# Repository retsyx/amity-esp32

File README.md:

# Amity for ESP32

HDMI-CEC that works!

Control your home theater with a familiar remote, and integrate it with Matter and HomeKit home automation.

Read the [rationale](doc/rationale.md), to know why Amity uses HDMI-CEC, and how it works.

This version runs on the Amity ESP32 board. The [original Amity](https://github.com/retsyx/amity) runs on a Raspberry Pi.

## Prerequisites

* An [Amity ESP32 board](hw/README.md) and a USB-C power supply.
* An extra HDMI cable. Amity uses two cables in place of the one connecting your receiver to your TV.
* A remote control. [Couch Clicker Atomic](https://github.com/retsyx/CouchClickerAtomic), [Couch Clicker Atomic 2](https://github.com/retsyx/CouchClickerAtomic2) or a Gen 2/3/4 Siri Remote.
* A Matter compatible home automation system.

## Amity is a flexible HDMI-CEC Controller (Not a Universal Remote)

### The Amity Adapter

Amity connects between home theater componenets using an HDMI Amity adapter. The adapter intercepts HDMI-CEC signals while passing through the HDMI A/V signals untouched. Each adapter has a `Display` HDMI connector that is connected to the display side and a `Source` HDMI connector that is connected to A/V source side.

### Single Adapter Amity

The single adapter Amity is designed for a traditional setup centered around an audio/video receiver (AVR). For example, a TV connected to a receiver output, and various playback devices (i.e. media streamers, blu-ray players, and game consoles, etc.) connected to the receiver's inputs. When changing the source, the input is changed on the receiver. The HDMI-CEC protocol only allows the designated TV to select sources or devices to declare themselves as active sources. TVs do not heed arbitrary source selection commands from other devices. As a result, Amity cannot select inputs on a TV, and cannot control sources connected directly to a TV, including built-in smart TV apps. Similarly, the singla adapter Amity does not support HDMI ARC/eARC. If you use smart TV apps or connect devices, other than a receiver, directly to the TV inputs, Amity is not for your system.

### Multi-Adapter Amity

Amity firmware is designed to support up to four Amity adapters. A multi-adapter Amity enables more applications. It can be used to control a system with two displays (for example, a TV and a projector) connected to a single receiver and to control a system without a receiver, where a TV is connected directly to multiple components, or where some components are connected to the TV and some are connected to a receiver. It can also be used to isolate particularly misbehaved components that demand to be displayed when not appropriate.

### Multi-Amity

Up to four Amities (with four adapters each) can be networked together over WiFi to control a large home theater setup containing more components than a single Amity can control or to control multiple physically separate systems with a single remote.

### Controlling Components Without HDMI-CEC

Amity can only control devices that support HDMI-CEC! However, devices that don't support HDMI-CEC (old game consoles, for example) can still be facilitated.

## Initial Amity Firmware Setup

For a new board, use the provisioning tool to prepare a firmware image and setup card, then install the image over USB. If your board already has Amity installed, continue with [Setup](#setup). To update an existing Amity, see [Firmware Updates](#firmware-updates).

### Download

1. Go to the latest [Amity Release](https://github.com/retsyx/amity-esp32/releases/latest).
2. From the release's **Assets**, download `amity-firmware.zip` and the setup-tool ZIP for your computer:

   | Computer | Setup tool |
   |---|---|
   | Apple Silicon Mac | `amity-provision-darwin-arm64.zip` |
   | Intel Mac | `amity-provision-darwin-amd64.zip` |
   | Windows, Intel/AMD | `amity-provision-windows-amd64.zip` |
   | Windows on ARM | `amity-provision-windows-arm64.zip` |
   | Linux, Intel/AMD | `amity-provision-linux-amd64.zip` |
   | Linux, ARM64 | `amity-provision-linux-arm64.zip` |
3. Extract the setup-tool ZIP into the same folder as `amity-firmware.zip`. Leave the firmware ZIP intact.
4. Open a terminal in that folder, and run the command below.

On macOS or Linux:

```sh
./amity-provision --hostname <amity hostname> --generate-password --out <output folder> amity-firmware.zip
```

On Windows, use PowerShell:

```powershell
.\amity-provision.exe --hostname <amity hostname> --generate-password --out <output folder> amity-firmware.zip
```

Choose a distinct name and output folder for each provisioned board.

The tool creates the output folder, containing:

* `amity-provisioned.bin` — the firmware image for USB installation.
* `amity-pairing.png` — a setup card with the Matter pairing QR code, Matter pairing code, browser address, and generated admin password.
* Text files with the same setup details and password.

For other options, including choosing your own password, see the [Amity provisioning guide](amity-provision/README.md).

If you lose the provisioning information for the board, you will need re-provision, wipe, and re-install the board from scratch!

Continue with [Initial Install over USB](#initial-install-over-usb).

### Build Locally

To build your own firmware, follow the [local build guide](BUILDING.md).

### Initial Install Over USB

1. Connect the Amity board to your computer with a USB data cable.
2. Install [esptool](https://docs.espressif.com/projects/esptool/en/latest/esp32s3/installation.html).
3. Find the board's serial port. Typical names are `COM3` on Windows, `/dev/cu.usbmodem...` on macOS, and `/dev/ttyACM0` on Linux.
4. Run this command with your provisioning output folder:

```sh
esptool --chip esp32s3 --port <port>> write-flash --flash-mode dio --flash-freq 80m --flash-size 8MB 0x0 <output folder>/amity-provisioned.bin
```

If the `esptool` command is unavailable, use `python3 -m esptool` on macOS/Linux, or `python -m esptool` on Windows, in its place.

**Installing this full image replaces all existing settings and pairings.** Use it for initial installation only. Later browser updates use a different file, `amity-update.bin`.

Installation is now done, and Amity can now be setup for use in your home theater.

## Setup

### HDMI Connections

Enable HDMI-CEC on all the home theater system components. Manufacturers use different names for this setting; check your equipment's setup menus.

#### Single Adapter Amity

The single adapter Amity connects between the TV and the receiver.

1. Disconnect the HDMI cable connecting the TV's input to the receiver's output.
2. Connect the TV's HDMI input to the Amity HDMI port marked `Display`.
3. Use a second HDMI cable to connect the receiver's HDMI output to the Amity HDMI port marked `Source`.
4. Leave the playback devices connected to the receiver's inputs.

#### Multi-Adapter Amity

There are many options for connecting a multi-adapter Amity. Generally, there will be at least one between the display and other components, whether with a receiver or without. In addition an adapter can be connected between a receiver and a component to isolate a misbehaving component. In all cases, the 'Display' side of an adapter should be connected towards the display, and the 'Source' side of an adapter should be connected towards the A/V source.

### Matter and WiFi enrollment

Amity must be enrolled with a Matter home automation system to operate and to join your WiFi network.

Amity Matter setup opens automatically at boot on a fresh board with no current Matter pairings; no button press is required. An Amity whose last Matter pairing was removed opens Matter setup again at boot.

Use the Matter pairing information from the provisioned setup card to complete Matter enrollment.

Once Amity is enrolled with Matter, it will join your WiFi network and configuration can continue on Amity's admin page.

Note: HomeKit (Apple Home) successfully enrolls Amity but the Home app will display the Amity accessory as `Not Supported`. HomeKit does not support Matter Media Media Playback accessories directly. The workaround for Amity is to add it again to HomeKit as a HomeKit native accessory. See [HomeKit](#homekit).

## Administering Amity

In your web browser open the Amity administration page. For example, if the setup card hostname `amity-1234`, then browse to `https://amity-1234.local` (on Mac) or `https://amity-1234` (on Windows). The web browser will prompt that the site may be unsafe. This is because Amity creates a self signed security certificate for encryption. It is safe. Click on the details, and accept that the site is safe. Enter the admin password provided in the setup card. If Amity was provisioned without an initial password, create one when prompted.

### Activity Configuration

An activity describes a use of your home theater, such as 'Watch Apple TV' or 'Play PlayStation'. It specifies a display, a source, and an audio device. Selecting the activity turns on the appropriate equipment and routes the remote's commands to those devices.

Ensure that HDMI-CEC is enabled on all equipment, select the 'Activities' tab, and press 'Scan HDMI'. On a new installation, Amity creates a suggested list of activities from the devices it finds. Review the names and device selections, then press 'Save activities'.

Devices are identified by their HDMI On Screen Display (OSD) names, owning Amity, adapter and side. Devices on the same side of an adapter must have distinct OSD names.

If a device is missing, check its HDMI-CEC setting and connections, then scan again. Some devices only appear while powered on. A source that does not reliably appear can sometimes be used through [receiver input selection](#non-cec-sources).

### Editing the List of Activities

Drag activities to change their order. The position in the list determines which remote shortcut starts the activity; see [Using Amity](#using-amity).

Use 'Add activity' to create an activity, 'Edit' to change one, and 'Delete' to remove one. Press 'Save activities' when finished. 'Discard changes' returns to the saved configuration.

### Editing an Activity

The fields of an activity are:

* `Name` — a descriptive name of your choice.
* `Display` — the screen, typically your TV.
* `Source` — the playback device, such as a streamer or game console.
* `Audio` — the device that receives volume and mute commands, typically your receiver.
* `Switch Device` — an optional receiver or switch used for explicit input selection.
* `Input` — the switch device input number, shown only when a switch device is specified. See [Non-CEC Sources](#non-cec-sources).

To specify equipment without discovery, type its OSD name and choose 'Add component...'; select its Amity, adapter and side, then add it.

Peess 'Save activities' to save the activity changes.

#### Strange Devices

HDMI-CEC devices can behave strangely. Here are some known workarounds.

##### Nintendo Switch

The Nintendo switch has a minimal HDMI-CEC implementation that appears to be nearly always dormant and ignores practically every command except standby. The Switch only appears when it is powered on directly by the user, or placed in the cradle, and then it automatically requests to be displayed.

As a result, the Switch will often not show up in device scans, or be auto-configured. The solution is to create a new activity for the Nintendo Switch:

1. Press the '+' button to create a new activity.
2. Write in the activity name, for example `Play Switch`
3. Select the appropriate Display, and Audio devices.
4. Enter `NintendoSwitch` in the `Source` device field.
5. Press 'OK', and then press 'Save'.

Then to play, turn on the Switch, and select the `Play Switch` activity on the remote. Amity will do the right thing when the Switch is woken up, and announces itself. To end the activity, press the power button on the Siri remote to place the entire system in standby, including the Switch, which will go dormant again.

Sometimes, however, this may not be enough, and the Switch may still not announce its presence. For this case, the Switch can be configured similarly to a [non-CEC source](#non-cec-sources).

##### Non-CEC Sources

Non-CEC and Non-HDMI sources can be minimally supported, if the receiver supports input selection over HDMI-CEC. An activity for a non-CEC source can still control the display and receiver, including power and volume, but cannot control the power of the non-CEC source or send it menu commands. This limited support is particularly useful for old game consoles that require the use of their own game controllers in any case so a universal remote to control them is of limited value.

To support a non-HDMI source, Amity can be configured to select the input on the receiver. In the activity settings:

1. Select the receiver as the `Switch Device`.
2. Specify the `Input` number.

This functionality depends on the receiver supporting the feature, and on knowing the correct value for the input. Often input numbers are listed in the receiver's setup menus.

### Pairing a Remote

Charge the remote, and unpair it from any other device before pairing it with Amity.

1. Select the 'Remote' tab, and press 'Pair remote'.
2. Hold the remote close to Amity.
3. Start pairing on the remote:

   | Remote | Pairing buttons |
   |---|---|
   | Couch Clicker Atomic | Hold **Power + Volume Up** for six seconds to clear the previous bond and pair again. [Remote guide](https://github.com/retsyx/CouchClickerAtomic) |
   | Siri Remote, generation 2 or 3 | Hold **Back + Volume Up** for five seconds. [Apple's pairing instructions](https://support.apple.com/en-us/102569) |

4. Wait for Amity to report that the remote is paired.

Amity selects a nearby supported remote automatically. If pairing times out, move the remote closer and try again. To unpair the remote press 'Unpair remote'.

### Matter

The initial Matter pairing connects Amity to Wi-Fi and adds it to your home controller. Once activities are configured, the Matter controller can use Amity for home automation.

The matter tab lists controller connections. To add another controller, press 'Start pairing' and scan the displayed QR code in that controller's home app. The pairing window lasts five minutes.

Available controls may include power, activity selection, playback, volume, mute, and remote battery status. What appears depends on the home app and your equipment.

### HomeKit

Unfortunately, HomeKit does not support Matter Media Playback accessories directly. To be able to control Amity with HomeKit and Apple's Remote app, Amity must be added as a HomeKit native accessory.

In the HomeKit tab, press 'Start pairing', and scan the pairing QR code with the Apple Home app. The pairing window lasts five minutes.

HomeKit has its own pairing code, separate from Matter.

### Adding an Amity to a Multi-Amity Setup

To add an uninitialized Amity to an existing Amity system, open the Amity devices tab, and press 'Add'. Hold the new Amity’s `RESET` button for approximately three seconds. Enter the new Amity's name, and add it.

Note that Amity administration continues solely on the main Amity. Additional boards are configured and controlled entirely by the main Amity.

### Backup & Restore

Open the `Advanced` tab. In the `Configuration` section, press `Download` to save a portable backup, or select a backup to preview its import.

The backup contains activities and device-specific control settings. It does not contain Wi-Fi settings, admin credentials, pairings, hostname changes, or the HDMI-CEC address. Keep the original installation folder as well; a configuration backup does not replace your pairing card or USB installation image.

### Firmware Updates

Note: Downgrades are unsupported.

1. Download  `amity-firmware.zip` from the latest [Amity Release](https://github.com/retsyx/amity-esp32/releases/latest).
2. Unzip `amity-firmware.zip`. The update binary in is `amity-update.bin`.
3. In the admin page, open the `Advanced` tab and press the `Update firmware` button. Select the downloaded `amity-update.bin` file and confirm the installation.
4. Keep all Amities powered as the update progresses. Once the update is complete, all Amities will restart together.

### Factory Reset

In the `Avdvanced` tab, press the `Factory reset` button and confirm. This clears activities, Wi-Fi settings, Matter and HomeKit pairings, and the remote bond. It also restores the original hostname and initial admin password, if one was provisioned.

Alternatively, while Amity is powered, press the physical `RESET` button for 10 seconds to factory reset Amity.

## Using Amity

Amity has two basic modes: standby, when no activity is selected, and active, when an activity is running.

### Standby

A short press of the `power` button starts the first activity. Other activity shortcuts depend on your remote:

| Remote | Short press | Long press |
|---|---|---|
| Atomic activity buttons | Activities 1–4 | Activities 5–8 |
| Siri Remote Select, Up, Right, Down, Left | Activities 1–5, in that order | Activities 6–10, in that order |

These shortcuts select activities by their current order in the list.

A long press of the `power` button repeats the standby command. This is useful if a device is still on when it should be off.

### Active

During an activity, navigation and playback buttons control the source. Volume and mute control the audio device. For example, in a PlayStation activity, the directional buttons navigate the PlayStation interface, while the volume buttons control the receiver. Siri Remote touchpad swipes also navigate the source's menus.

A short press of the `power` button ends the activity and puts the system in standby. A long press repeats the current activity's setup. Use this if a device failed to turn on or selected the wrong input. The Activites tab `Repair` button in the browser performs the same action.

To change activities on Siri Remote, hold the `power` and press an activity-selection button. You can also select an activity in the browser.

Give your equipment a few seconds to finish switching before choosing a different activity. If Amity ignores the selection while the system is settling, press again after the transition finishes.

## License

Amity source code is licensed under the [GPLv3](https://github.com/retsyx/amity-esp32/blob/main/LICENSE). See the [third-party notices](https://github.com/retsyx/amity-esp32/blob/main/THIRD_PARTY.md) for dependency licenses.

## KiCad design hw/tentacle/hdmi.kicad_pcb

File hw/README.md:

# Amity Hardware

There are a two variants of Amity hardware to choose from. Both are based on the [XIAO ESP32-S3 board](https://wiki.seeedstudio.com/xiao_esp32s3_getting_started/) because it offers a complete, inexpensive, compact solution. Other ESP32-S3 boards and even other ESP32 devices are also likely viable with the firmware's requirements of at least 512K SRAM and at least 1MB PSRAM, WiFi and BLE support. The combined memory requirement is approximately 1.2MB.

Each hardware directory has the full design along with the manufacturing outputs for PCB production and assembly.

## Single Adapter Amity ESP32

The simplest board with an ESP32 and a single HDMI adapter on a single PCB.

Design is [here](board/).

## Multi Adapter Amity

Two PCBs. One with the ESP32 and four RJ-45 connectors for the 4 adapters, and a PCB for each adapter.

The main PCB, an 'octopus', is [here](octopus/).

The adapter PCB, a 'tentacle', is [here](tentacle/).

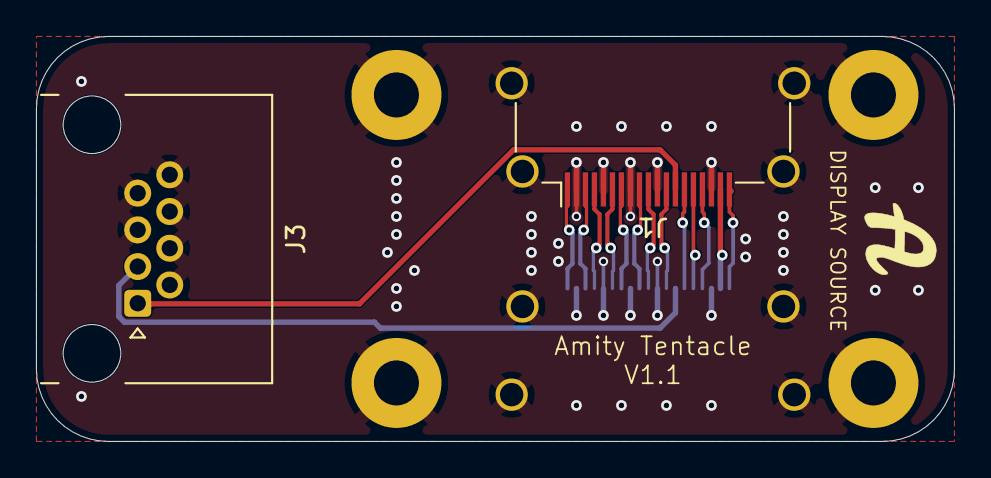
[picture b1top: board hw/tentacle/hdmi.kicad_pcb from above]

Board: 4 copper layers, 51.0 x 22.5 mm, 7 parts (1 on the bottom side), 16 nets.

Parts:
H1, H2, H3, H4: MountingHole_2.5mm_Pad
J1, J2: HDMI_A; HDMI_A_Amphenol_10029449-x01xLF_Horizontal
J3: RJ45; RJ45_Pulse_E5J88-00LJG2-L_Horizontal_EdgeMount

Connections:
/CK+: J1.10 (CK+), J2.10 (CK+)
/CK-: J1.12 (CK-), J2.12 (CK-)
/D0+: J1.7 (D0+), J2.7 (D0+)
/D0-: J1.9 (D0-), J2.9 (D0-)
/D1+: J1.4 (D1+), J2.4 (D1+)
/D1-: J1.6 (D1-), J2.6 (D1-)
/D2+: J1.1 (D2+), J2.1 (D2+)
/D2-: J1.3 (D2-), J2.3 (D2-)
GND: H1.1 (1_1), H2.1 (1_1), H3.1 (1_1), H4.1 (1_1), J1.2 (D2S), J1.5 (D1S), J1.8 (D0S), J1.11 (CKS), J1.17 (GND), J1.SH, J2.2 (D2S), J2.5 (D1S), J2.8 (D0S), J2.11 (CKS), J2.17 (GND), J2.SH, J3.2, J3.4, J3.5, J3.6, J3.7, J3.8
unnamed: J1.18 (+5V), J2.18 (+5V)
unnamed: J1.13 (CEC), J3.1
unnamed: J1.19 (HPD), J2.19 (HPD)
unnamed: J1.15 (SCL), J2.15 (SCL)
unnamed: J1.16 (SDA), J2.16 (SDA)
unnamed: J1.14 (UTILITY), J2.14 (UTILITY)
unnamed: J2.13 (CEC), J3.3

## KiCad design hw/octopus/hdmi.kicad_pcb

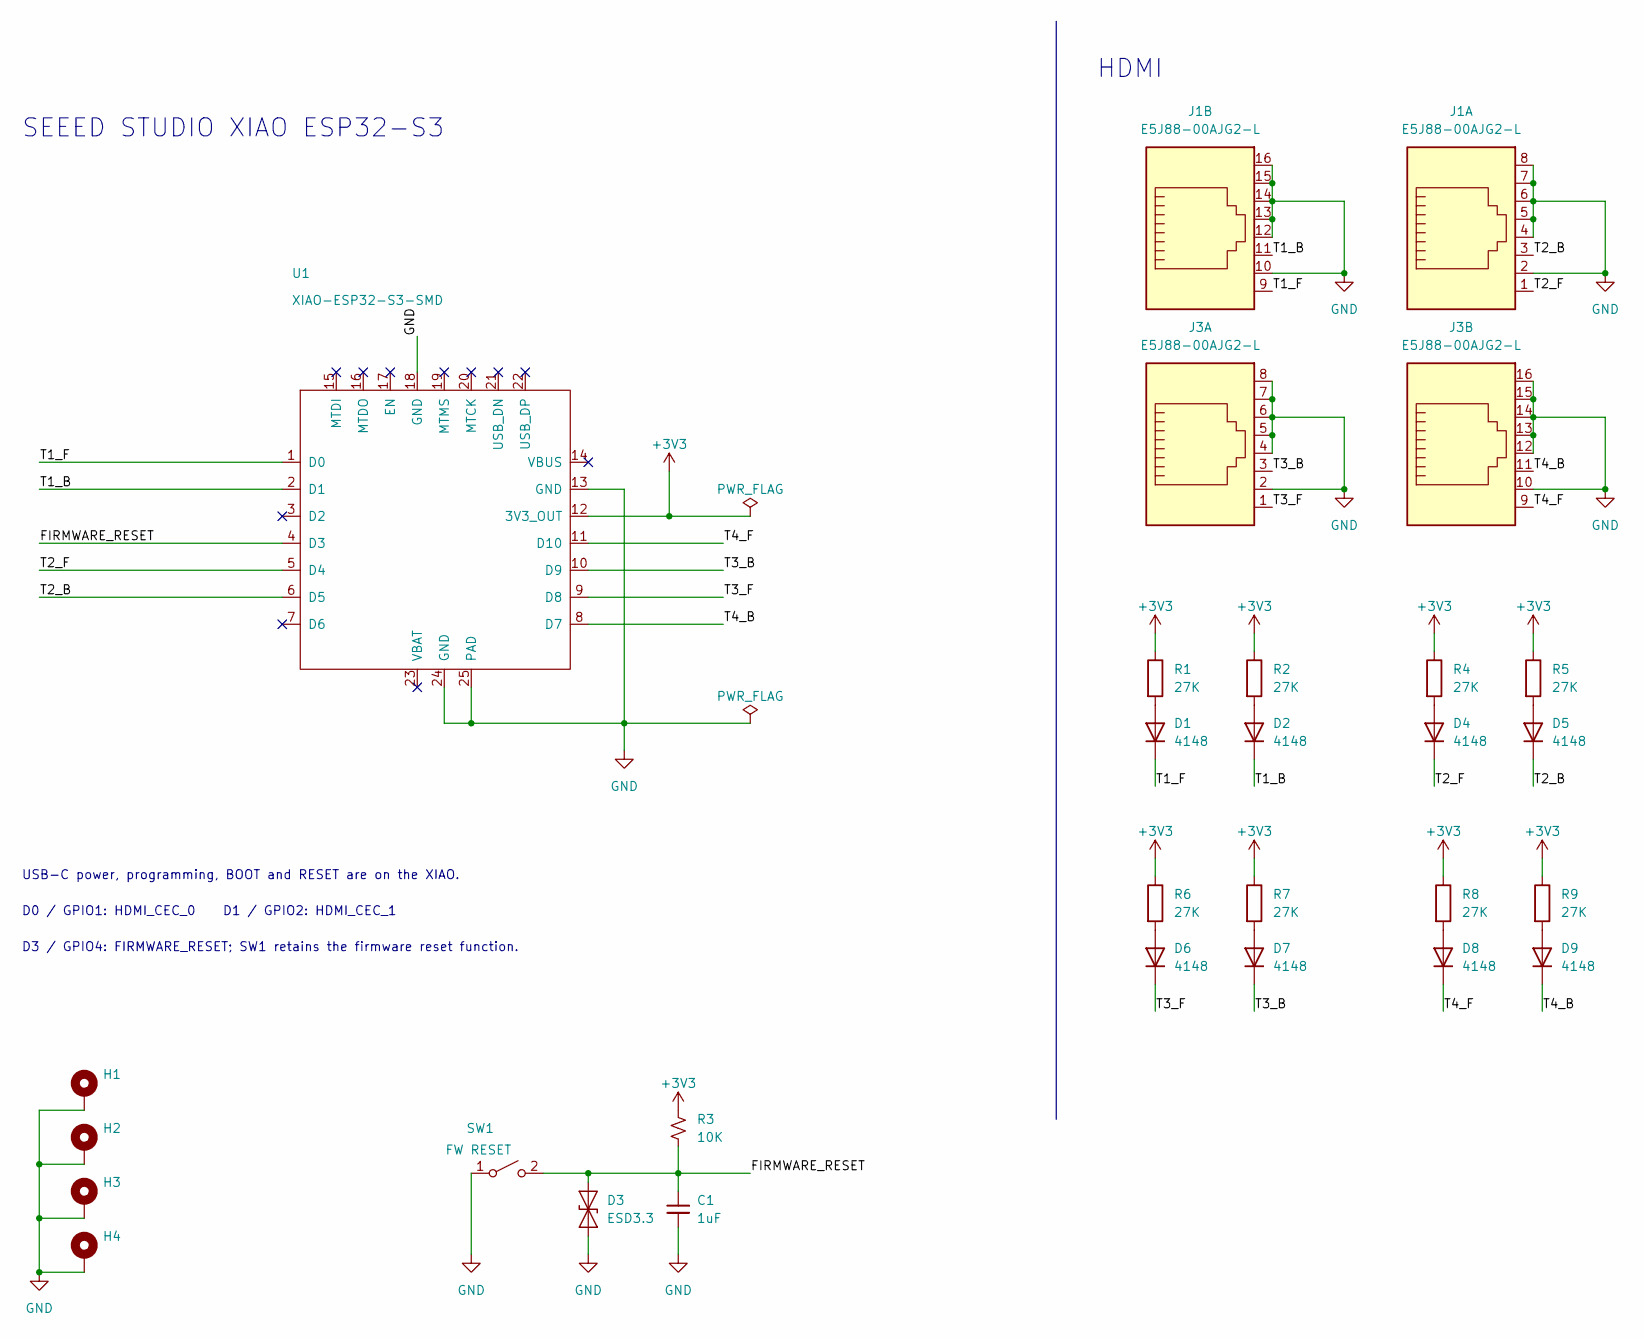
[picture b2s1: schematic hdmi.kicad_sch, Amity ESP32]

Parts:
C1: 1uF; C_0603_1608Metric; Tolerance 10%; Voltage Rating 16 V; MPN C1608X7R1C105K080AC
D1, D2, D4, D5, D6, D7, D8, D9: 4148; D_0603_1608Metric; MPN TS4148 RCG
D3: ESD3.3; D_SOD-923; MPN ESD9B3.3ST5G
H1, H2, H3, H4: MountingHole_2.5mm_Pad
J1, J3: E5J88-00AJG2-L; RJ45_Pulse_E5J88-00AJG2-L_Horizontal_EdgeMount
R1, R2, R4, R5, R6, R7, R8, R9: 27K; R_0603_1608Metric; Tolerance 5%; Power Rating 0.1 W; MPN CR0603-JW-273ELF
R3: 10K; R_0603_1608Metric; Tolerance 1%; Power Rating 0.1 W; MPN CR0603-FX-1002ELF
SW1: FW RESET; SW_SPST_B3U-1000P; MPN B3U-1000P
U1: XIAO-ESP32-S3-SMD; MPN 113991114

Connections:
+3V3: R1.1, R2.1, R3.1, R4.1, R5.1, R6.1, R7.1, R8.1, R9.1, U1.12 (3V3_OUT)
/FIRMWARE_RESET: C1.1, D3.2 (A2), R3.2, SW1.2 (B), U1.4 (D3)
/T1_B: D2.1 (K), J1.11, U1.2 (D1)
/T1_F: D1.1 (K), J1.9, U1.1 (D0)
/T2_B: D5.1 (K), J1.3, U1.6 (D5)
/T2_F: D4.1 (K), J1.1, U1.5 (D4)
/T3_B: D7.1 (K), J3.3, U1.10 (D9)
/T3_F: D6.1 (K), J3.1, U1.9 (D8)
/T4_B: D9.1 (K), J3.11, U1.8 (D7)
/T4_F: D8.1 (K), J3.9, U1.11 (D10)
GND: C1.2, D3.1 (A1), H1.1 (1_1), H2.1 (1_1), H3.1 (1_1), H4.1 (1_1), J1.2, J1.4, J1.5, J1.6, J1.7, J1.8, J1.10, J1.12, J1.13, J1.14, J1.15, J1.16, J3.2, J3.4, J3.5, J3.6, J3.7, J3.8, J3.10, J3.12, J3.13, J3.14, J3.15, J3.16, SW1.1 (A), U1.13 (GND), U1.18 (GND), U1.24 (GND), U1.25 (PAD)
unnamed: D1.2 (A), R1.2
unnamed: D2.2 (A), R2.2
unnamed: D4.2 (A), R4.2
unnamed: D5.2 (A), R5.2
unnamed: D6.2 (A), R6.2
unnamed: D7.2 (A), R7.2
unnamed: D8.2 (A), R8.2
unnamed: D9.2 (A), R9.2

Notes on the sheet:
HDMI
D3 / GPIO4: FIRMWARE_RESET; SW1 retains the firmware reset function.
SEEED STUDIO XIAO ESP32-S3
D0 / GPIO1: HDMI_CEC_0 D1 / GPIO2: HDMI_CEC_1
USB-C power, programming, BOOT and RESET are on the XIAO.

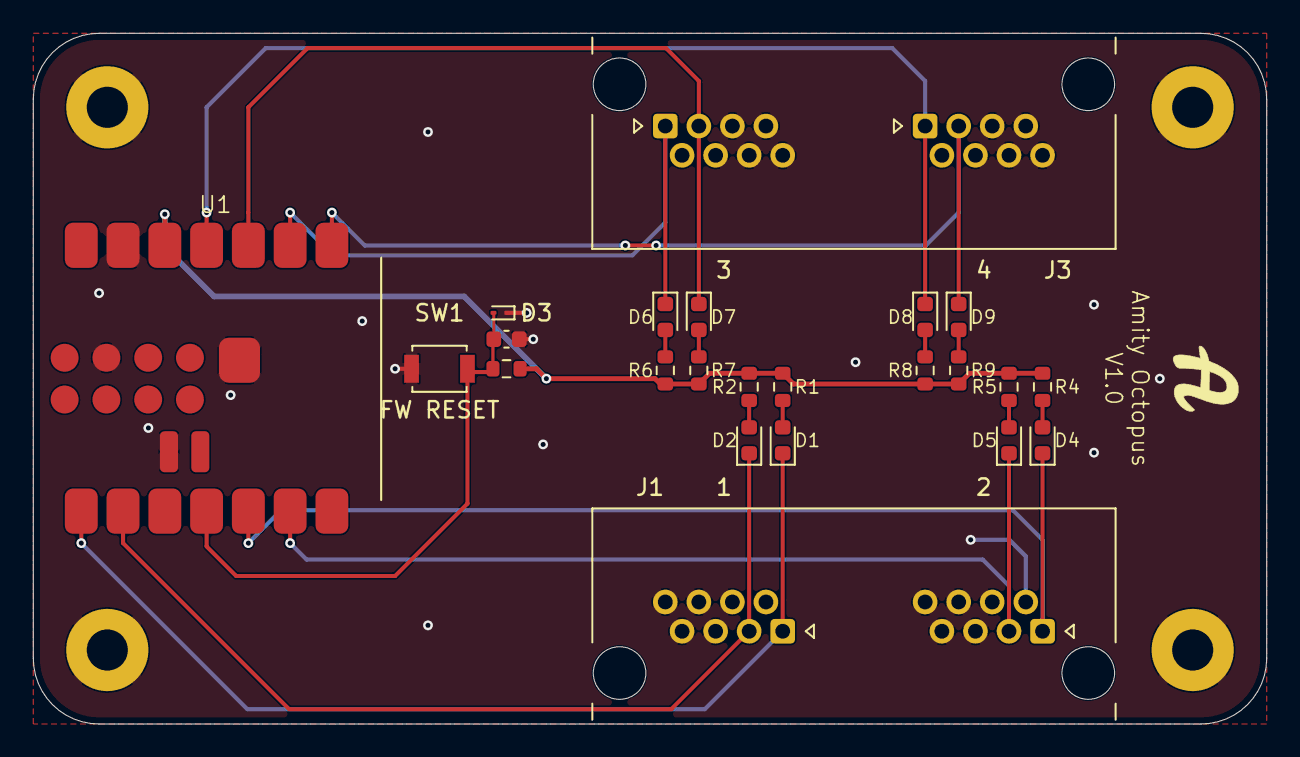
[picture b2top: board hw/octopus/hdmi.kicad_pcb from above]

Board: 2 copper layers, 75.0 x 42.0 mm, 27 parts (0 on the bottom side), 19 nets.

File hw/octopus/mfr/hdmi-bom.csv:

"Reference","Quantity","Value","Manufacturer","MPN","Footprint","Description","Tolerance","Voltage Rating","Power Rating","Dielectric","Datasheet","Assembly Notes"
"C1","1","1uF","TDK","C1608X7R1C105K080AC","Capacitor_SMD:C_0603_1608Metric","1 uF ceramic capacitor, 10%, 16 V, X7R, 0603, 0.8 mm height","10%","16 V","","X7R","https://product.tdk.com/system/files/dam/doc/product/capacit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",""
"D1,D2,D4,D5,D6,D7,D8,D9","8","4148","Taiwan Semiconductor","TS4148 RCG","Diode_SMD:D_0603_1608Metric","Fast switching diode, 75 V, 100 mA, 4 ns, ceramic 0603","","","","","https://services.taiwansemi.com/storage/resources/datasheet/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",""
"D3","1","ESD3.3","onsemi","ESD9B3.3ST5G","Diode_SMD:D_SOD-923","Bidirectional ESD protection diode, 3.3 V standoff, SOD-923","","","","","https://www.onsemi.com/download/data-sheet/pdf/esd9b-d.pdf",""
"J1,J3","2","E5J88-00AJG2-L","","","Pulse_Electronics:RJ45_Pulse_E5J88-00AJG2-L_Horizontal_EdgeMount","Dual unshielded RJ45 jack, 2 ports of 8 contacts, horizontal through-hole","","","","","https://www.mouser.com/datasheet/2/447/E5J88_00AJG2_L-2902971.pdf",""
"R1,R2,R4,R5,R6,R7,R8,R9","8","27K","Bourns","CR0603-JW-273ELF","Resistor_SMD:R_0603_1608Metric","27 kohm thick-film resistor, 5%, 0.1 W, 0603","5%","","0.1 W","","https://www.bourns.com/docs/Product-Datasheets/chpreztr.pdf",""
"R3","1","10K","Bourns","CR0603-FX-1002ELF","Resistor_SMD:R_0603_1608Metric","10 kohm thick-film resistor, 1%, 0.1 W, 0603","1%","","0.1 W","","https://www.bourns.com/docs/Product-Datasheets/chpreztr.pdf",""
"SW1","1","FW RESET","Omron Electronic Components","B3U-1000P","Button_Switch_SMD:SW_SPST_B3U-1000P","SPST-NO momentary tactile switch, top actuation, 1.5 N, SMT, without locating boss","","","","","https://omronfs.omron.com/en_US/ecb/products/pdf/en-b3u.pdf",""
"U1","1","XIAO-ESP32-S3-SMD","Seeed Studio","113991114","Seeed_Studio_XIAO_Series:XIAO-ESP32-S3-SMD","XIAO ESP32-S3 module, 8 MB flash, 8 MB PSRAM, USB-C, 21 x 17.8 mm","","","","","https://files.seeedstudio.com/Bazaar/product_pdf/113991114.pdf",""

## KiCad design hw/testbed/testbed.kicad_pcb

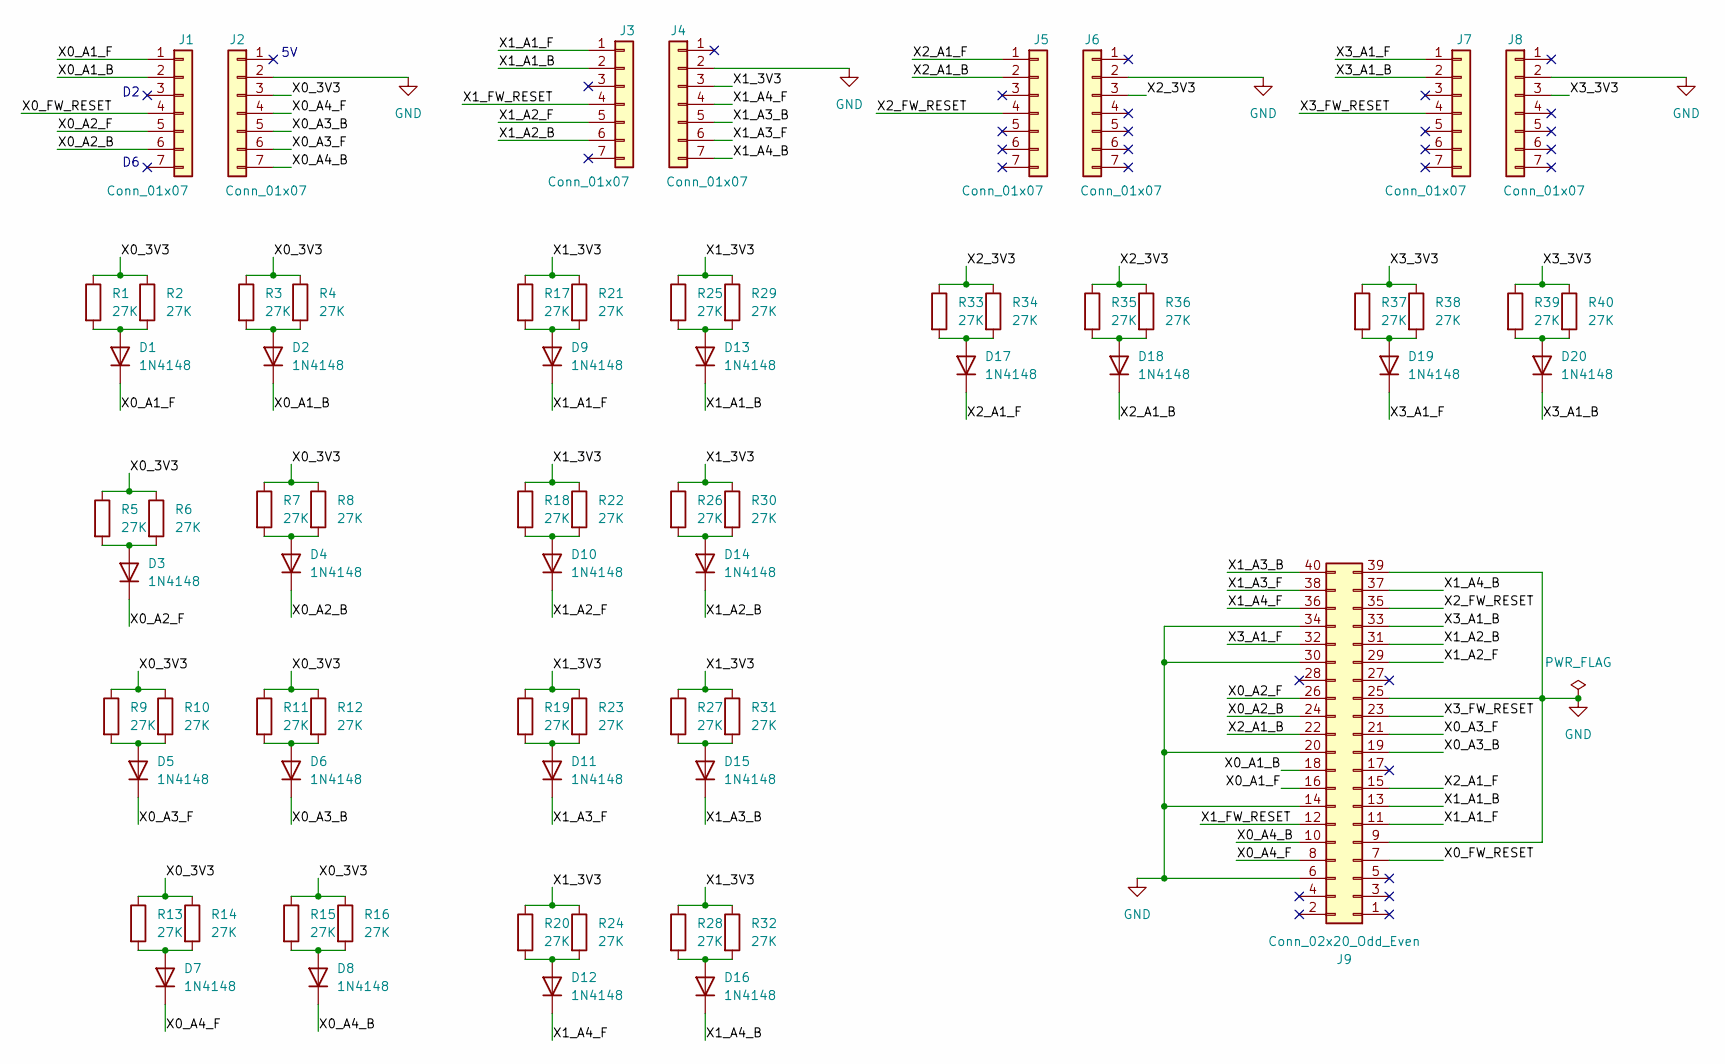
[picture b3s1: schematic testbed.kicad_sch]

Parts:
D1, D2, D3, D4, D5, D6, D7, D8, D9, D10, D11, D12, D13, D14, D15, D16, D17, D18, D19, D20: 1N4148; D_DO-35_SOD27_P7.62mm_Horizontal
J1, J2, J3, J4, J5, J6, J7, J8: Conn_01x07; PinSocket_1x07_P2.54mm_Vertical
J9: Conn_02x20_Odd_Even; PinSocket_2x20_P2.54mm_Vertical
R1, R2, R3, R4, R5, R6, R7, R8, R9, R10, R11, R12, R13, R14, R15, R16, R17, R18, R19, R20, R21, R22, R23, R24, R25, R26, R27, R28, R29, R30, R31, R32, R33, R34, R35, R36, R37, R38, R39, R40: 27K; R_Axial_DIN0207_L6.3mm_D2.5mm_P7.62mm_Horizontal

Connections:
/X0_3V3: J2.3, R1.1, R2.1, R3.1, R4.1, R5.1, R6.1, R7.1, R8.1, R9.1, R10.1, R11.1, R12.1, R13.1, R14.1, R15.1, R16.1
/X0_A1_B: D2.1 (K), J1.2, J9.18
/X0_A1_F: D1.1 (K), J1.1, J9.16
/X0_A2_B: D4.1 (K), J1.6, J9.24
/X0_A2_F: D3.1 (K), J1.5, J9.26
/X0_A3_B: D6.1 (K), J2.5, J9.19
/X0_A3_F: D5.1 (K), J2.6, J9.21
/X0_A4_B: D8.1 (K), J2.7, J9.10
/X0_A4_F: D7.1 (K), J2.4, J9.8
/X0_FW_RESET: J1.4, J9.7
/X1_3V3: J4.3, R17.1, R18.1, R19.1, R20.1, R21.1, R22.1, R23.1, R24.1, R25.1, R26.1, R27.1, R28.1, R29.1, R30.1, R31.1, R32.1
/X1_A1_B: D13.1 (K), J3.2, J9.13
/X1_A1_F: D9.1 (K), J3.1, J9.11
/X1_A2_B: D14.1 (K), J3.6, J9.31
/X1_A2_F: D10.1 (K), J3.5, J9.29
/X1_A3_B: D15.1 (K), J4.5, J9.40
/X1_A3_F: D11.1 (K), J4.6, J9.38
/X1_A4_B: D16.1 (K), J4.7, J9.37
/X1_A4_F: D12.1 (K), J4.4, J9.36
/X1_FW_RESET: J3.4, J9.12
/X2_3V3: J6.3, R33.1, R34.1, R35.1, R36.1
/X2_A1_B: D18.1 (K), J5.2, J9.22
/X2_A1_F: D17.1 (K), J5.1, J9.15
/X2_FW_RESET: J5.4, J9.35
/X3_3V3: J8.3, R37.1, R38.1, R39.1, R40.1
/X3_A1_B: D20.1 (K), J7.2, J9.33
/X3_A1_F: D19.1 (K), J7.1, J9.32
/X3_FW_RESET: J7.4, J9.23
GND: J2.2, J4.2, J6.2, J8.2, J9.6, J9.9, J9.14, J9.20, J9.25, J9.30, J9.34, J9.39
unnamed: D1.2 (A), R1.2, R2.2
unnamed: D2.2 (A), R3.2, R4.2
unnamed: D3.2 (A), R5.2, R6.2
unnamed: D4.2 (A), R7.2, R8.2
unnamed: D5.2 (A), R9.2, R10.2
unnamed: D6.2 (A), R11.2, R12.2
unnamed: D7.2 (A), R13.2, R14.2
unnamed: D8.2 (A), R15.2, R16.2
unnamed: D9.2 (A), R17.2, R21.2
unnamed: D10.2 (A), R18.2, R22.2
unnamed: D11.2 (A), R19.2, R23.2
unnamed: D12.2 (A), R20.2, R24.2
unnamed: D13.2 (A), R25.2, R29.2
unnamed: D14.2 (A), R26.2, R30.2
unnamed: D15.2 (A), R27.2, R31.2
unnamed: D16.2 (A), R28.2, R32.2
unnamed: D17.2 (A), R33.2, R34.2
unnamed: D18.2 (A), R35.2, R36.2
unnamed: D19.2 (A), R37.2, R38.2
unnamed: D20.2 (A), R39.2, R40.2

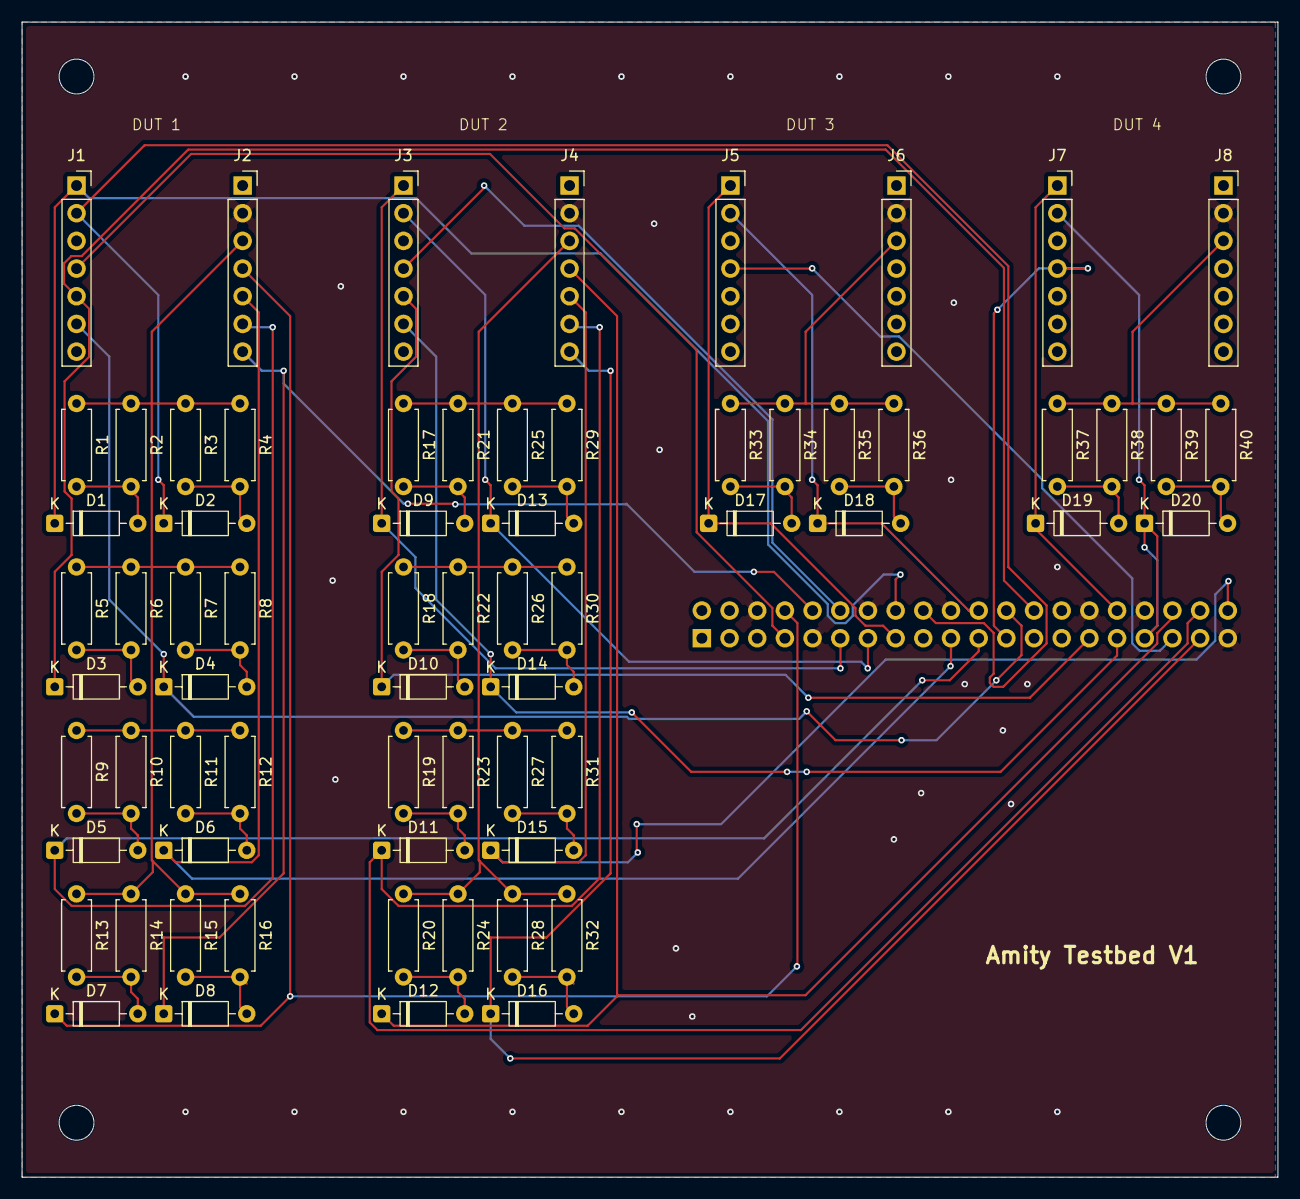
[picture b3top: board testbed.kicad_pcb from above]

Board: 2 copper layers, 115.2 x 106.0 mm, 73 parts (1 on the bottom side), 49 nets.

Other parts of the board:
H1, H2, H3, H4: MountingHole_3.2mm_M3
